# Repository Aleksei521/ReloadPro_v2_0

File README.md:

# ReloadPro-LCD-128x64.<br>
ReloadPro for LCD 128x64(PCF8535).<br>
Fork of https://github.com/arachnidlabs/reload-pro<br>
Change display to 128x64 on the controller PCF8535.<br>
Change IDE version to v4.2<br>
Add temperarure measure on NTC resistor.<br>
Add control COOLER.<br>
Add push-pull isolated converter from USB 5V to 5V and 12V for COOLER.<br>

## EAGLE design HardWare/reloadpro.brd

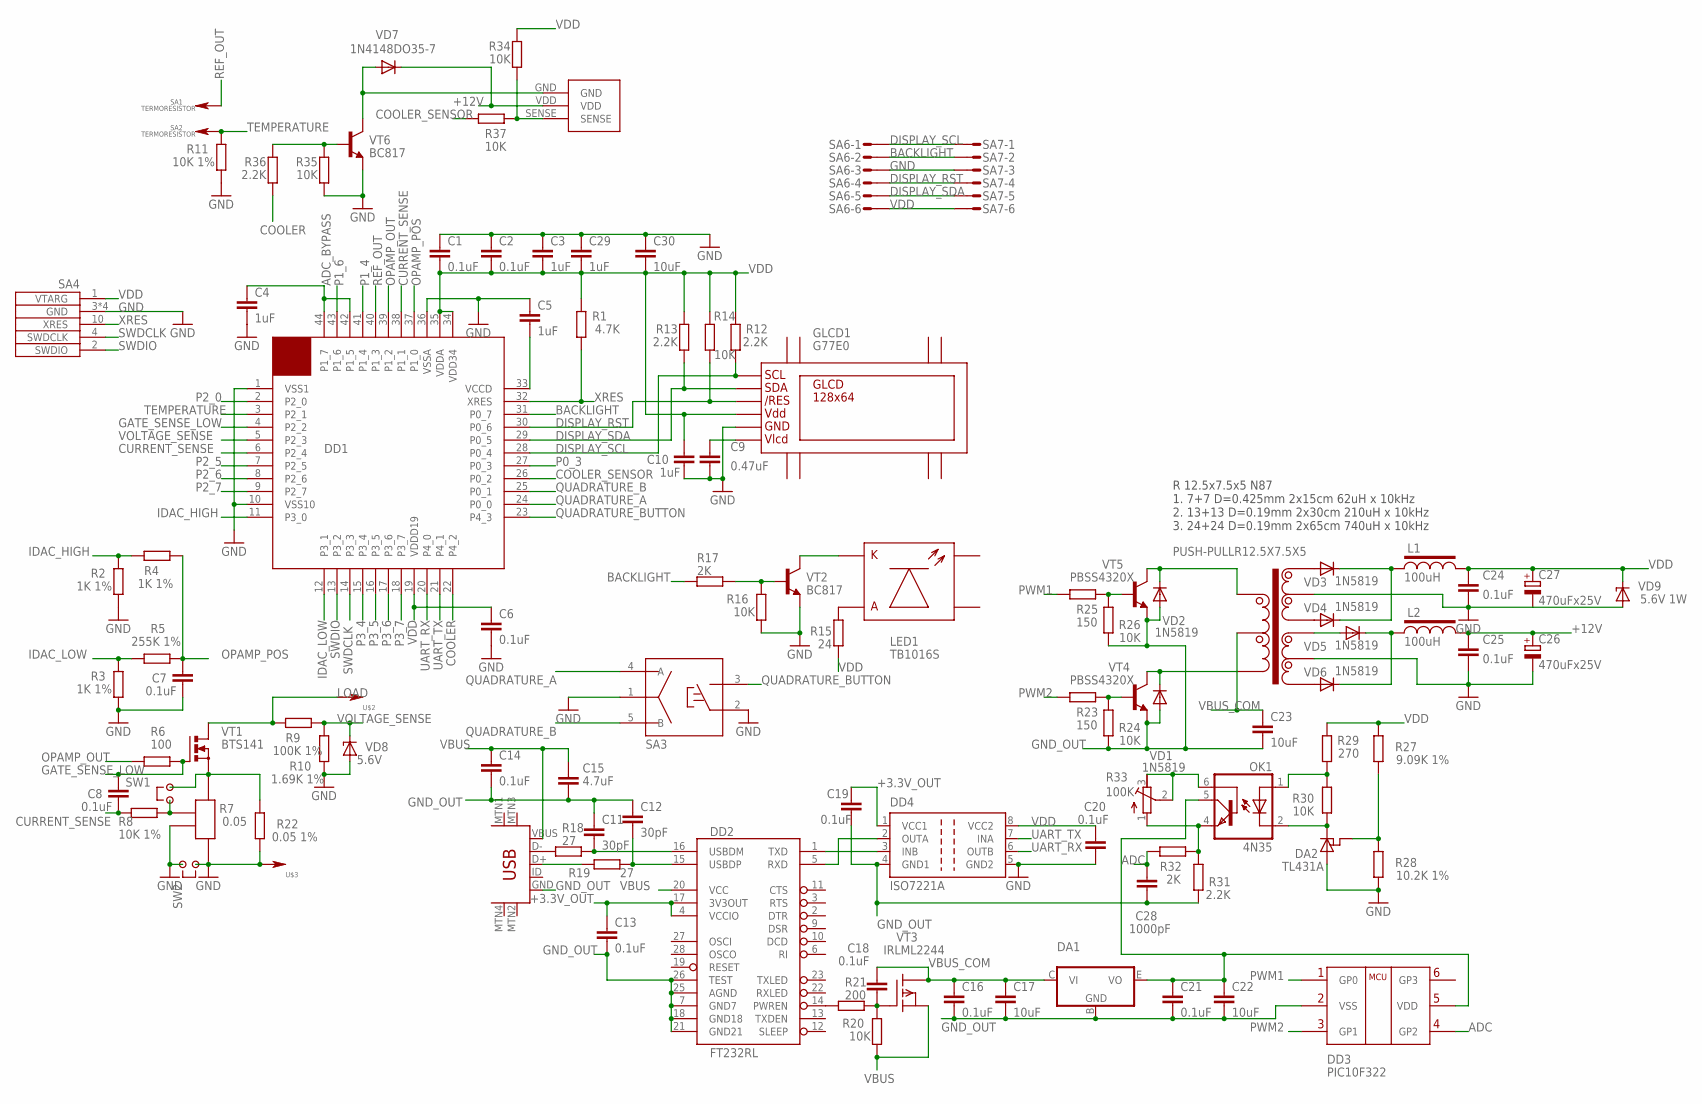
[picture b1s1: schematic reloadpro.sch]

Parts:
C1, C2, C6, C7, C8, C13, C14, C16, C18, C19, C20, C21, C24: 0.1uF; C0603
C3, C4, C5, C10, C29: 1uF; C0603
C9: 0.47uF; C1206
C11, C12: 30pF; C0603
C15: 4.7uF; C0805
C17, C22, C23: 10uF; C1206
C25: 0.1uF; C0805
C26, C27: 470uFx25V; E3,5-8
C28: 1000pF; C0805
C30: 10uF; C0805
DA1: 78GOR; TO92-EBC
DA2: TL431A; TO92-EBC
DD1: CY8C4245-AXITQFP44; TQFP44
DD2: FT232RL; SSOP28DB
DD3: PIC10F322; SOT23-6
DD4: ISO7221A; SO-08
GLCD1: G77E0
L1, L2: 100uH; LGA0410
LED1: TB1016S
OK1: 4N35; DIL06
R1: 4.7K; R0603
R2, R3, R4: 1K 1%; R0603
R5: 255K 1%; R0805
R6: 100; R0805
R7: 0.05; SR10
R8, R11: 10K 1%; R0603
R9: 100K 1%; R0603
R10: 1.69K 1%; R0805
R12, R13, R31, R36: 2.2K; R0603
R14, R16, R20, R24, R26, R30, R34, R35, R37: 10K; R0603
R15: 24; R1206
R17, R32: 2K; R0603
R18, R19: 27; R0805
R21: 200; R0603
R22: 0.05 1%; R2512
R23, R25: 150; R0805
R27: 9.09K 1%; R0805
R28: 10.2K 1%; R0805
R29: 270; R0805
R33: 100K; RTRIM3296H
SA1, SA2: TERMORESISTOR; 1-PIN_HOME
SA3: PEC16IDC; PEC16-IDC
SA4: SWDSMD; IDC10_1.27SMD
SA5: 3-PIN-COOLER
SA6, SA7: MICROMATCH-6SMD
SW1, SW2: 2-PINDIL; 2-PIN
TR1: PUSH-PULLR12.5X7.5X5; R12.5X7.5X5PUSHH-PULL
U$1: USB-MINIB-5PIN; USB-MINIB
U$2, U$3: 1-PIN2_54; 1_PIN_2_54
VD1, VD2, VD3, VD4, VD5, VD6: 1N5819; DO41-10
VD7: 1N4148DO35-7; DO35-7
VD8: 5.6V; STABILITRON
VD9: 5.6V 1W; DO35-10
VT1: BTS141; TO220BV
VT2, VT6: BC817; SOT23-BEC
VT3: IRLML2244; SOT23
VT4, VT5: PBSS4320X; SOT89-BCE

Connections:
+3.3V_OUT: C13.1, C19.1, DD2.4 (VCCIO), DD2.17 (3V3OUT), DD4.1 (VCC1)
+12V: C25.1, C26.+, L2.P$2 (L2), SA5.VDD, VD7.C
ADC: C28.1, DD3.4 (GP2), R32.1
ADC_BYPASS: C4.1, DD1.42 (P1_5), DD1.44 (P1_7)
BACKLIGHT: DD1.31 (P0_7), R17.2, SA6.2, SA7.2
COOLER: DD1.22 (P4_2), R36.1
COOLER_SENSOR: DD1.26 (P0_2), R37.2
CURRENT_SENSE: C8.2, DD1.6 (P2_4), DD1.38 (P1_1), R8.2
DISPLAY_RST: DD1.30 (P0_6), GLCD1./RES, R14.1, SA6.4, SA7.4
DISPLAY_SCL: DD1.28 (P0_4), GLCD1.SCL, R12.1, SA6.1, SA7.1
DISPLAY_SDA: DD1.29 (P0_5), GLCD1.SDA, R13.1, SA6.5, SA7.5
GATE_SENSE_LOW: C8.1, DD1.4 (P2_2), R6.1, VT1.G
GND: C1.1, C2.1, C3.1, C4.2, C5.1, C6.2, C7.2, C9.2, C10.2, C20.2, C24.2, C25.2, C26.-, C27.-, C29.1, C30.1, DA2.B (A), DD1.1 (VSS1), DD1.10 (VSS10), DD1.36 (VSSA), DD4.5 (GND2), GLCD1.GND, R2.1, R3.1, R7.1, R7.2, R10.2, R11.1, R16.1, R22.2, R28.2, R35.1, SA3.1 (C), SA3.2 (B2), SA4.3 (GND), SA4.5 (GND), SA4.7 (GND), SA4.9 (GND), SA6.3, SA7.3, SW2.1, SW2.2, TR1.W2-COM, TR1.W2-COM1 (W2-COM), TR1.W3-COM, TR1.W3-COM1 (W3-COM), U$3.P$1, VD8.A, VD9.A, VT2.E, VT6.E
GND_OUT: C11.1, C12.1, C13.2, C14.2, C15.2, C16.2, C17.2, C19.2, C21.2, C22.2, C23.2, C28.2, DA1.B (GND), DD2.7 (GND7), DD2.18 (GND18), DD2.21 (GND21), DD2.25 (AGND), DD2.26 (TEST), DD3.2 (VSS), DD4.4 (GND1), R24.1, R26.1, R31.2, U$1.GND, VD1.A, VD2.A, VT4.E, VT5.E
IDAC_HIGH: DD1.11 (P3_0), R2.2, R4.2
IDAC_LOW: DD1.12 (P3_1), R3.2, R5.2
LOAD: R9.2, U$2.P$1, VT1.D
unnamed: C5.2, DD1.33 (VCCD)
unnamed: R7.4, R22.1, SW1.2, VT1.S
unnamed: R7.3, R8.1, SW1.1
unnamed: LED1.A, R15.1
unnamed: LED1.K, VT2.C
unnamed: R16.2, R17.1, VT2.B
unnamed: R18.1, U$1.D-
unnamed: C11.2, DD2.16 (USBDM), R18.2
unnamed: C9.1, GLCD1.VLCD
unnamed: R19.1, U$1.D+
unnamed: C12.2, DD2.15 (USBDP), R19.2
unnamed: DD2.1 (TXD), DD4.3 (INB)
unnamed: DD2.5 (RXD), DD4.2 (OUTA)
unnamed: DD2.14 (PWREN), R21.2
unnamed: C18.1, R20.2, R21.1, VT3.1 (G)
unnamed: C21.1, C22.1, DA1.E (VO), DD3.5 (VDD), OK1.5 (COL)
unnamed: R23.2, R24.2, VT4.B
unnamed: R34.1, R37.1, SA5.SENSE
unnamed: R25.2, R26.2, VT5.B
unnamed: TR1.W2-1, VD3.A
unnamed: TR1.W2-2, VD4.A
unnamed: TR1.W3-2, VD6.A
unnamed: TR1.W3-1, VD5.A
unnamed: L1.P$1 (L1), VD3.C, VD4.C
unnamed: L2.P$1 (L1), VD5.C, VD6.C
unnamed: DA2.E (REF), R27.2, R28.1
unnamed: OK1.1 (A), R29.2, R30.1
unnamed: DA2.C, OK1.2 (C), R30.2
unnamed: OK1.4 (EMI), R31.1, R32.2, R33.1 (E)
unnamed: OK1.6 (BAS), R33.2 (S), R33.3 (A)
unnamed: R35.2, R36.2, VT6.B
unnamed: SA5.GND, VD7.A, VT6.C
OPAMP_OUT: DD1.39 (P1_2), R6.2
OPAMP_POS: C7.1, DD1.37 (P1_0), R4.1, R5.1
P0_3: DD1.27 (P0_3)
P1_4: DD1.41 (P1_4)
P1_6: DD1.43 (P1_6)
P2_0: DD1.2 (P2_0)
P2_5: DD1.7 (P2_5)
P2_6: DD1.8 (P2_6)
P2_7: DD1.9 (P2_7)
P3_4: DD1.15 (P3_4)
P3_5: DD1.16 (P3_5)
P3_6: DD1.17 (P3_6)
P3_7: DD1.18 (P3_7)
PWM1: DD3.1 (GP0), R25.1
PWM1PWR: TR1.W1-1, VD2.C, VT5.C
PWM2: DD3.3 (GP1), R23.1
PWM2PWR: TR1.W1-2, VD1.C, VT4.C
QUADRATURE_A: DD1.24 (P0_0), SA3.4 (A)
QUADRATURE_B: DD1.25 (P0_1), SA3.5 (B)
QUADRATURE_BUTTON: DD1.23 (P4_3), SA3.3 (B1)
REF_OUT: DD1.40 (P1_3), SA1.P$1
SWDCLK: DD1.14 (P3_3), SA4.4 (SWDCLK)
SWDIO: DD1.13 (P3_2), SA4.2 (SWDIO)
TEMPERATURE: DD1.3 (P2_1), R11.2, SA2.P$1
UART_RX: DD1.20 (P4_0), DD4.6 (OUTB)
UART_TX: DD1.21 (P4_1), DD4.7 (INA)
VBUS: C14.1, C15.1, DD2.20 (VCC), R20.1, U$1.VBUS, VT3.2 (S)
VBUS_COM: C16.1, C17.1, C18.2, C23.1, DA1.C (VI), TR1.W1-COM, TR1.W1-COM1 (W1-COM), VT3.3 (D)
VDD: C1.2, C2.2, C3.2, C6.1, C10.1, C20.1, C24.1, C27.+, C29.2, C30.2, DD1.19 (VDDD19), DD1.34 (VDD34), DD1.35 (VDDA), DD4.8 (VCC2), GLCD1.VDD, L1.P$2 (L2), R1.2, R12.2, R13.2, R14.2, R15.2, R27.1, R29.1, R34.2, SA4.1 (VTARG), SA6.6, SA7.6, VD9.C
VOLTAGE_SENSE: DD1.5 (P2_3), R9.1, R10.1, VD8.C
XRES: DD1.32 (XRES), R1.1, SA4.10 (XRES)

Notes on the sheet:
R 12.5x7.5x5 N87 1. 7+7 D=0.425mm 2x15cm 62uH x 10kHz 2. 13+13 D=0.19mm 2x30cm 210uH x 10kHz 3. 24+24 D=0.19mm 2x65cm 740uH x 10kHz

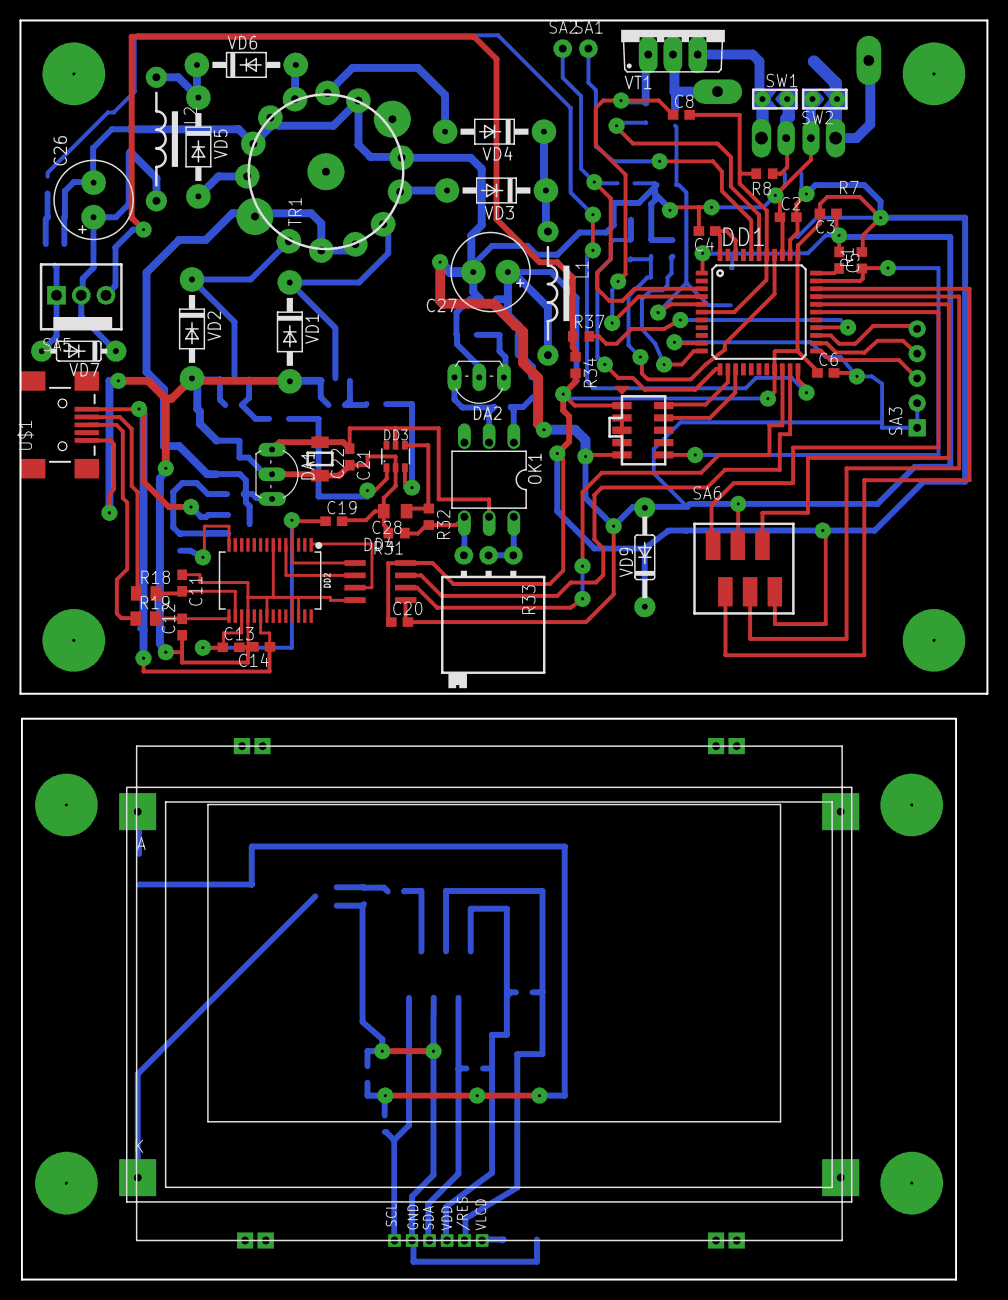
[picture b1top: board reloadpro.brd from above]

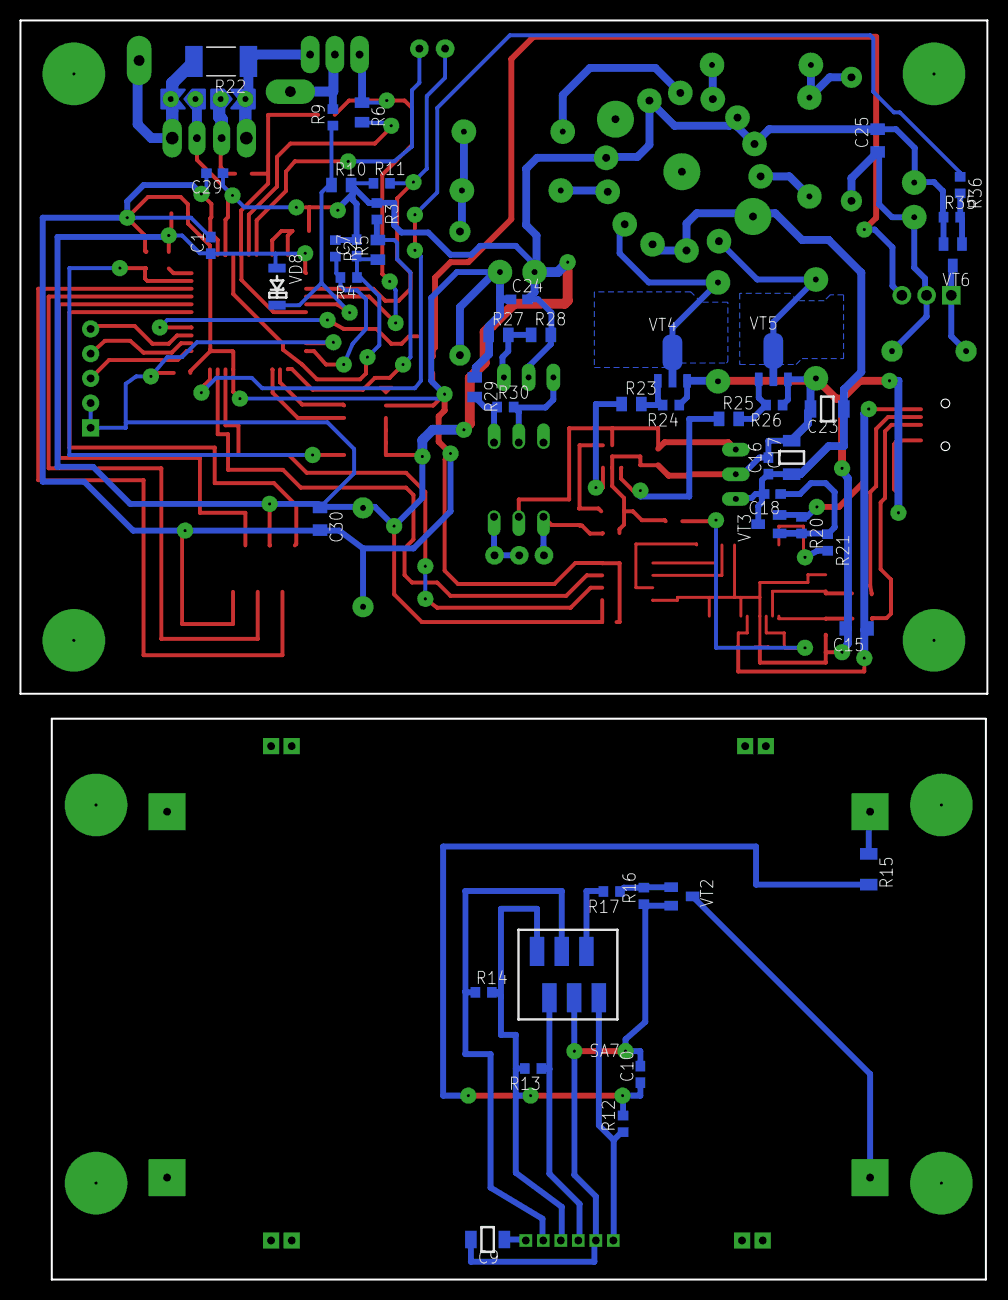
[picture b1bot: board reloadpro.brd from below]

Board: 2 copper layers, 99.4 x 129.4 mm, 106 parts (47 on the bottom side), 69 nets.

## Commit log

2019-10-13 Work Version tested on real hardware
    Work Version tested on real hardware
2019-10-13 Add project file
    add project file
